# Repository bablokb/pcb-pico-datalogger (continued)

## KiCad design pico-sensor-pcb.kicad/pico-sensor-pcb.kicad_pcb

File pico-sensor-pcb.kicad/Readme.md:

KiCAD-Designfiles for Sensor-PCB
================================

Here are the KiCAD (v6) design-files for the sensor-pcb.

Target components:

  - connectors to pico-datalogger-v2 pcb
  - AHT20
  - BH1750
  - PDM mic
  - connectors for I2C (Adafruit + Pimoroni layout)
  - ON button
  - RUN button
  - 4 buttons or LEDs

Schematic
---------

Layout
------

3D-Views
--------

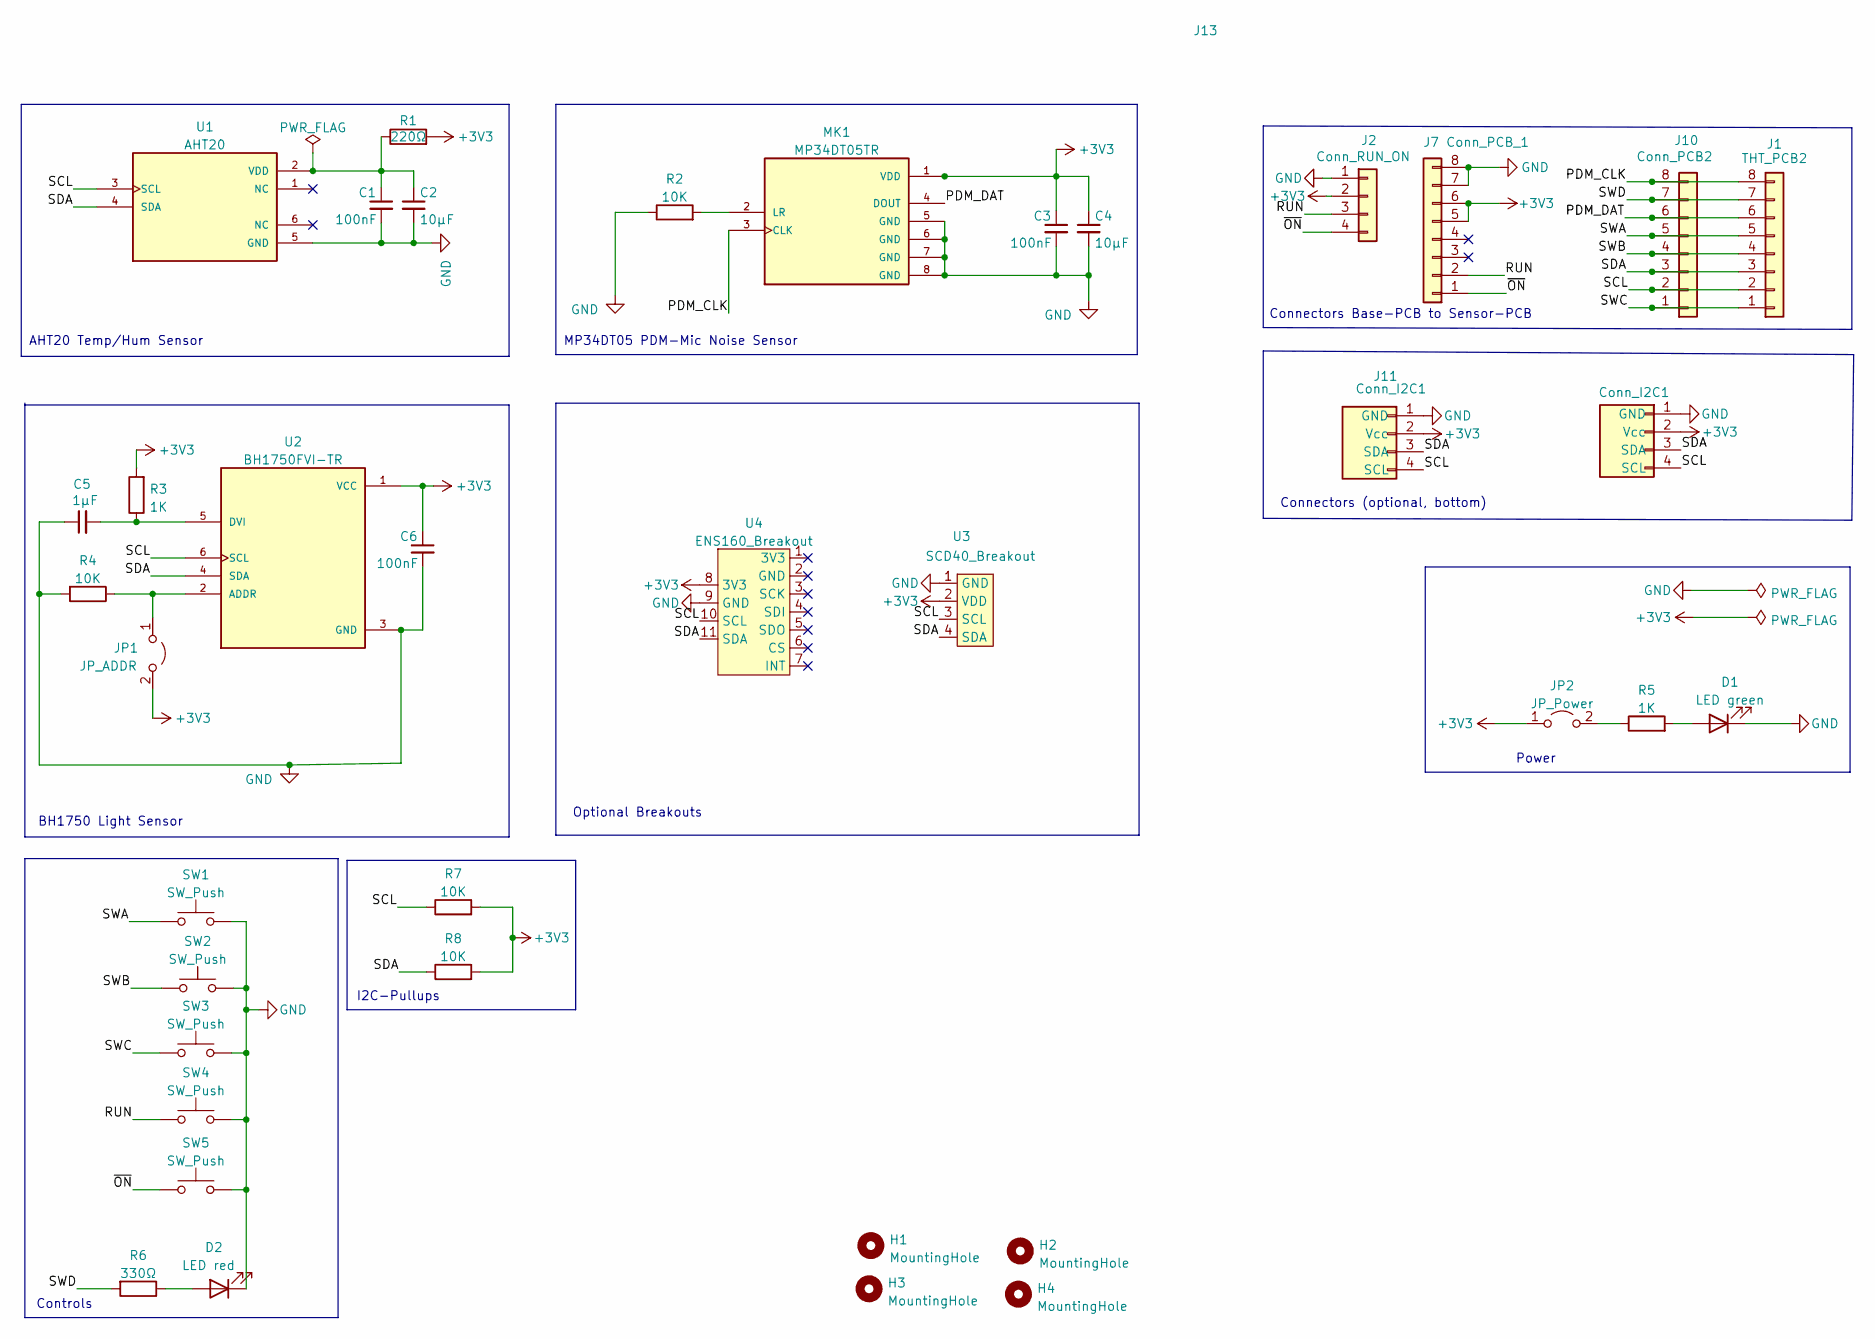
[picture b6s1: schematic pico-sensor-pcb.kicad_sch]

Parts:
C1, C3, C6: 100nF; C_0402_1005Metric; LCSC C1525
C2, C4: 10µF; C_0603_1608Metric; LCSC C19702
C5: 1µF; C_0603_1608Metric; LCSC C15849
D1: LED green; LED_0805_2012Metric; LCSC C2297
D2: LED red; LED_0805_2012Metric; LCSC C84256
H1, H2, H3, H4: MountingHole; MountingHole_2.5mm
J1: THT_PCB2; PinHeader_1x08_P2.54mm_Vertical
J2: Conn_RUN_ON; PinHeader_1x04_P2.54mm_Vertical
J7: Conn_PCB_1; JST_SUR_BM08B-SURS-TF_1x08-1MP_P0.80mm_Vertical; LCSC C5143489
J10: Conn_PCB2; JST_SUR_BM08B-SURS-TF_1x08-1MP_P0.80mm_Vertical; LCSC C5143489
J11: Conn_I2C1; JST_SH_SM04B-SRSS-TB_1x04-1MP_P1.00mm_Horizontal; LCSC C160404
J13: Conn_I2C1; PinHeader_1x04_P2.54mm_Horizontal
JP1: JP_ADDR; SolderJumper-2_P1.3mm_Open_Pad1.0x1.5mm
JP2: JP_Power; SolderJumper-2_P1.3mm_Open_Pad1.0x1.5mm
MK1: MP34DT05TR; LCSC C2688664
R1: 220Ω; R_0402_1005Metric; LCSC C25091
R2, R4, R7, R8: 10K; R_0402_1005Metric; LCSC C25744
R3, R5: 1K; R_0402_1005Metric; LCSC C11702
R6: 330Ω; R_0402_1005Metric; LCSC C25104
SW1, SW2, SW3, SW4, SW5: SW_Push; SW_SPST_B3S-1000; LCSC C221869
U1: AHT20; LCSC C3012622
U2: BH1750FVI-TR; BH1750; LCSC C78960
U3: SCD40_Breakout
U4: ENS160_Breakout

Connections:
+3V3: C3.1, C4.1, C6.1, J2.2, J7.5, J7.6, J11.2 (Vcc), J13.2 (Vcc), JP1.2 (B), JP2.1 (A), MK1.1 (VDD), R1.2, R3.2, R7.2, R8.2, U2.1 (VCC), U3.2 (VDD), U4.8 (3V3)
/PDM_CLK: J1.8, J10.8, MK1.3 (CLK)
/PDM_DAT: J1.6, J10.6, MK1.4 (DOUT)
/RUN: J2.3, J7.2, SW4.1
/SCL: J1.2, J10.2, J11.4 (SCL), J13.4 (SCL), R7.1, U1.3 (SCL), U2.6 (SCL), U3.3 (SCL), U4.10 (SCL)
/SDA: J1.3, J10.3, J11.3 (SDA), J13.3 (SDA), R8.1, U1.4 (SDA), U2.4 (SDA), U3.4 (SDA), U4.11 (SDA)
/SWA: J1.5, J10.5, SW1.1
/SWB: J1.4, J10.4, SW2.1
/SWC: J1.1, J10.1, SW3.1
/SWD: J1.7, J10.7, R6.2
/~ON: J2.4, J7.1, SW5.1
GND: C1.2, C2.2, C3.2, C4.2, C5.1, C6.2, D1.1 (K), D2.1 (K), J2.1, J7.7, J7.8, J11.1 (GND), J13.1 (GND), MK1.5 (GND), MK1.6 (GND), MK1.7 (GND), MK1.8 (GND), R2.1, R4.2, SW1.2, SW2.2, SW3.2, SW4.2, SW5.2, U1.5 (GND), U2.3 (GND), U3.1 (GND), U4.9 (GND)
unnamed: C1.1, C2.1, R1.1, U1.2 (VDD)
unnamed: C5.2, R3.1, U2.5 (DVI)
unnamed: D1.2 (A), R5.2
unnamed: D2.2 (A), R6.1
unnamed: JP1.1 (A), R4.1, U2.2 (ADDR)
unnamed: JP2.2 (B), R5.1
unnamed: MK1.2 (LR), R2.2

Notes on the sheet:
Optional Breakouts
AHT20 Temp/Hum Sensor
BH1750 Light Sensor
MP34DT05 PDM-Mic Noise Sensor
Power
Connectors (optional, bottom)
I2C-Pullups
Controls
Connectors Base-PCB to Sensor-PCB

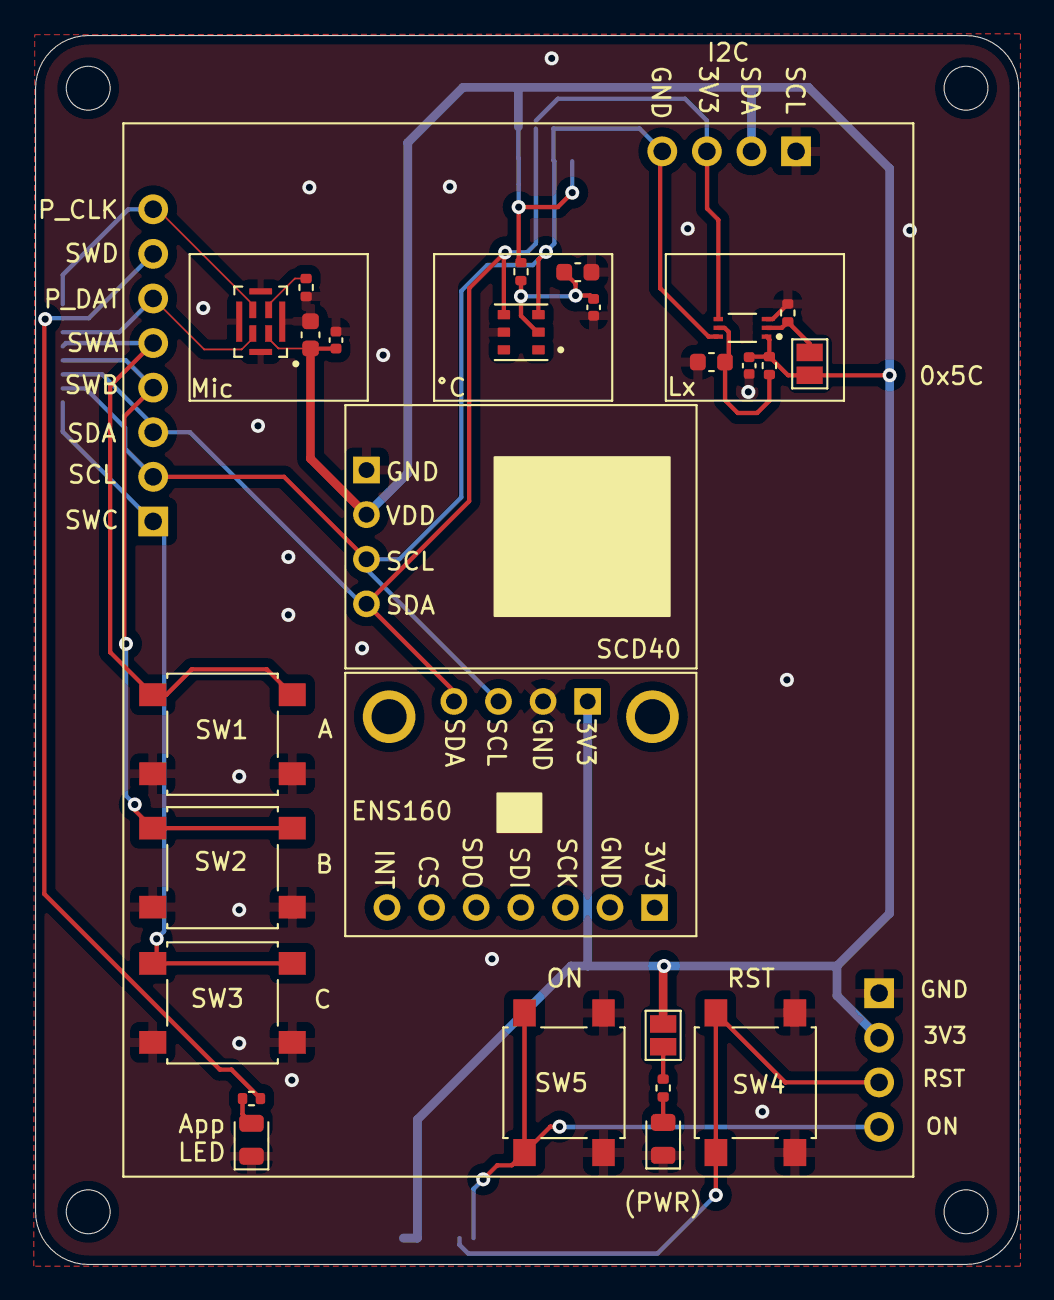
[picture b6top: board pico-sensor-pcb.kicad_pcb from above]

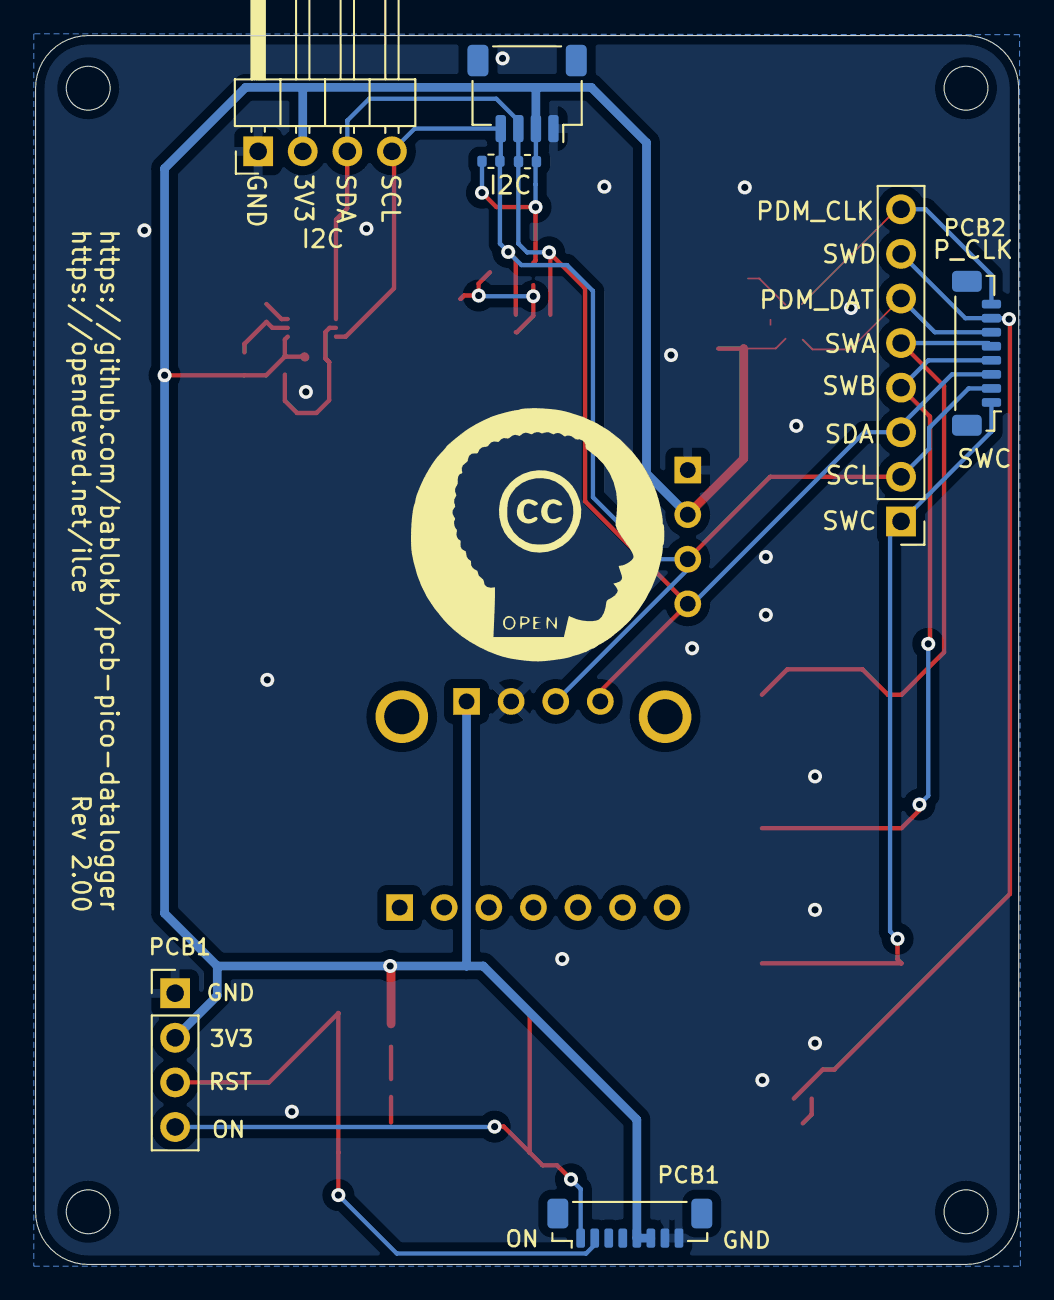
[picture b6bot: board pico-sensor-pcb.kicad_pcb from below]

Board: 2 copper layers, 56.0 x 70.0 mm, 38 parts (8 on the bottom side), 19 nets.

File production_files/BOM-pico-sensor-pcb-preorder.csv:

Comment,Designator,Footprint,LCSC
1K,"R3,R5",R_0402_1005Metric,C11702
100nF,"C1,C3,C6",C_0402_1005Metric,C1525
1µF,C5,C_0603_1608Metric,C15849
Conn_I2C1,J11,JST_SH_SM04B-SRSS-TB_1x04-1MP_P1.00mm_Horizontal,C160404
10µF,"C2,C4",C_0603_1608Metric,C19702
SW_Push,"SW1,SW2,SW3,SW4,SW5",SW_SPST_B3S-1000,C221869
LED green,D1,LED_0805_2012Metric,C2297
220Ω,R1,R_0402_1005Metric,C25091
330Ω,R6,R_0402_1005Metric,C25104
10K,"R2,R4,R7,R8",R_0402_1005Metric,C25744
MP34DT05TR,MK1,MP34DT05TR,C2688664
AHT20,U1,AHT20,C2757850
Conn_PCB2,"J10,J7",JST_SUR_BM08B-SURS-TF_1x08-1MP_P0.80mm_Vertical,C5143489
BH1750FVI-TR,U2,BH1750,C78960
LED red,D2,LED_0805_2012Metric,C84256

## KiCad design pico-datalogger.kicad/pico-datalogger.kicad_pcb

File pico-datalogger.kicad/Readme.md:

KiCAD-Designfiles
=================

This branch contains KiCAD v7 files. The PCB layout has been adjusted to fit a 10th inch grid. The only significant adjustment was to move SWA, SWB, SWC to a new location.

The diagrams below are for the older version KiCAD (v6). 

Schematic
---------

Layout
------

3D-Views
--------

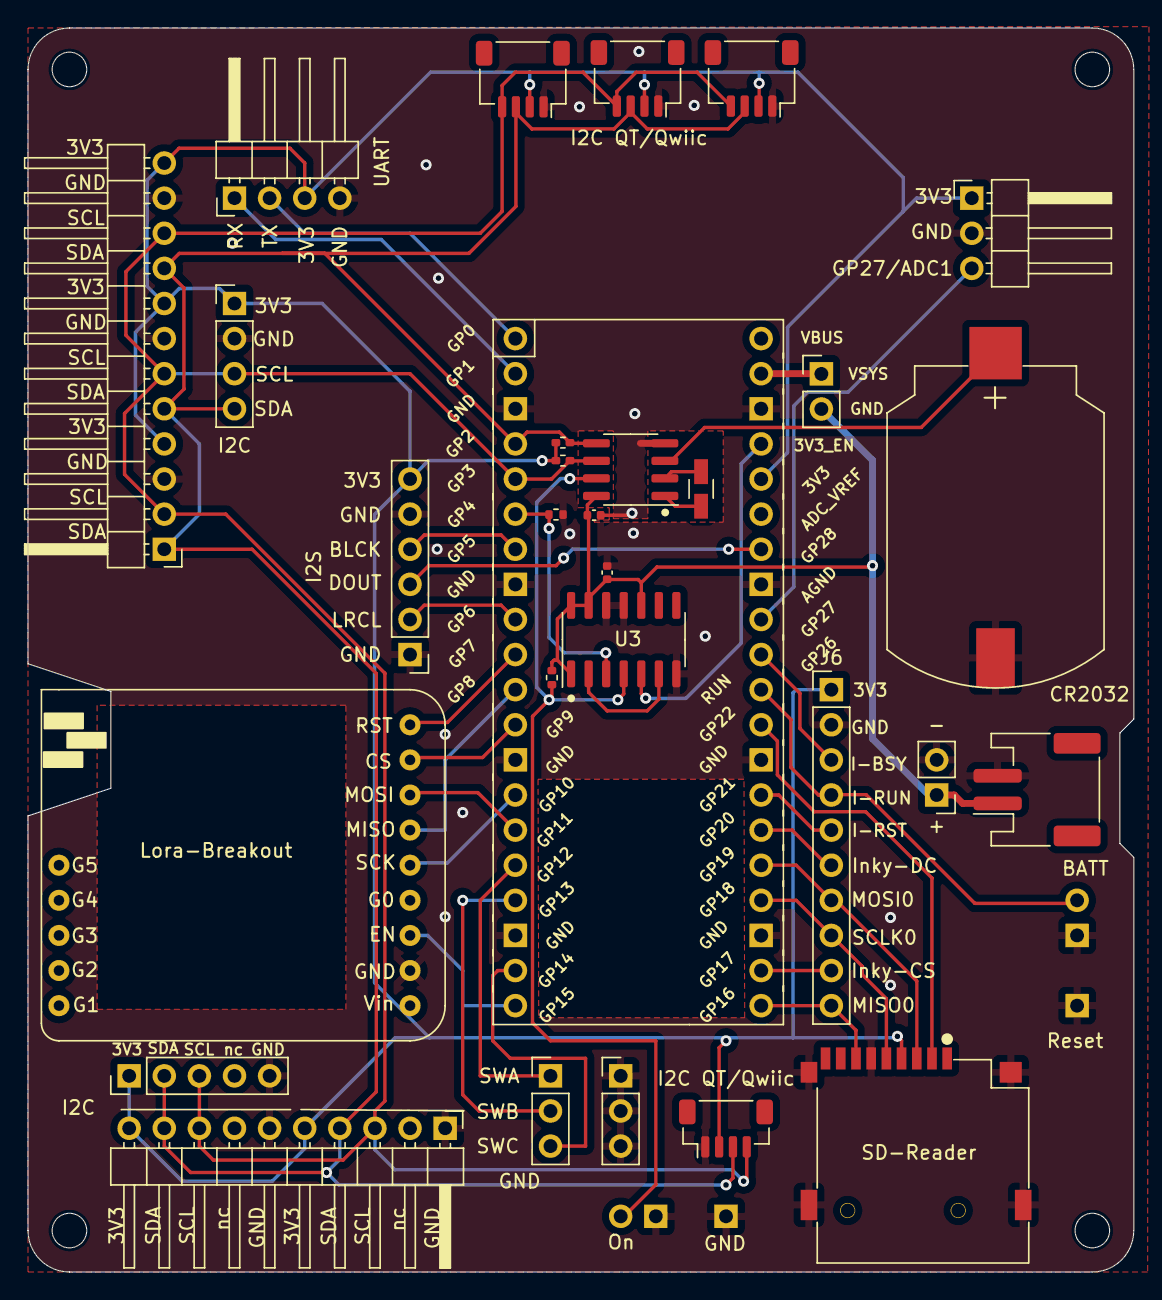
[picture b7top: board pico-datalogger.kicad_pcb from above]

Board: 2 copper layers, 80.0 x 90.0 mm, 36 parts (0 on the bottom side), 37 nets.

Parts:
BT1: Coin_Cell; CR2032_Holder
C1, C2: 100nF; C_0402_1005Metric
H1, H2, H3, H4: MountingHole; MountingHole_2.5mm
J1: JST-PH2 VCC; JST_PH_S2B-PH-SM4-TB_1x02-1MP_P2.00mm_Horizontal
J2: I2C_8; JST_SH_SM04B-SRSS-TB_1x04-1MP_P1.00mm_Horizontal
J3: RFM9x_Lora_Breakout
J4: Alt-VCC; PinHeader_1x02_P2.54mm_Vertical
J5: Conn_I2S; PinHeader_1x06_P2.54mm_Vertical
J6: Conn_Inky_SPI; PinHeader_1x10_P2.54mm_Vertical
J7: Micro_SD_TF_PUSH; TF-Push
J8: Conn_ADC; PinHeader_1x03_P2.54mm_Horizontal
J9: Conn_UART; PinHeader_1x04_P2.54mm_Horizontal
J10: Conn_Inky_SW; PinHeader_1x03_P2.54mm_Vertical
J11: I2C_1; PinHeader_1x12_P2.54mm_Horizontal
J12: I2C_7; JST_SH_SM04B-SRSS-TB_1x04-1MP_P1.00mm_Horizontal
J14: I2C_6; JST_SH_SM04B-SRSS-TB_1x04-1MP_P1.00mm_Horizontal
J16: BG_2; PinHeader_1x05_P2.54mm_Vertical
J18: I2C_5; JST_SH_BM04B-SRSS-TB_1x04-1MP_P1.00mm_Vertical
J19: I2C_4; PinHeader_1x04_P2.54mm_Vertical
J20: BG_3; PinHeader_1x10_P2.54mm_Horizontal
J21: Conn_GND; PinHeader_1x03_P2.54mm_Vertical
JP1: Jumper_VSYS; PinHeader_1x02_P2.54mm_Vertical
R1: 100K; R_0402_1005Metric
R2, R3, R4: 10K; R_0402_1005Metric
SW1: SW_Push_SLIM; SW_PUSH_SLIM_1x4
SW2: SW_Reset; SW_PUSH_SLIM_1x4
U1: SN74HC74N; SOIC-14_3.9x8.7mm_P1.27mm
U2: PCF8523T; SOIC-8_3.9x4.9mm_P1.27mm
U3: Pico; RPi_Pico_TH_nodbg
Y1: Crystal; Crystal_SMD_3215-2Pin_3.2x1.5mm

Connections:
+3V3: J2.2 (Vcc), J3.1 (VIN), J5.6, J6.1, J7.4 (VDD), J8.1, J9.3, J11.4, J11.8, J11.12, J12.2 (Vcc), J14.2 (Vcc), J16.1, J18.2 (Vcc), J19.1, J20.5, J20.10, R3.1, R4.1, U3.36 (3V3)
+BATT: C1.1, C2.1, J1.1, J4.1, JP1.2 (B), R2.1, U1.1 (1~CLR), U1.10 (2~PRE), U1.13 (2~CLR), U1.14 (VCC), U2.8 (VDD)
/1~PRE: R2.2, SW1.2, U1.4 (1~PRE), U2.7 (~INT1/CLKOUT)
/3V3_EN: U1.5 (1Q), U3.37 (3V3_EN)
/BLCK: J5.4, U3.7 (GPIO5)
/DOUT: J5.3, U3.34 (GPIO28_ADC2)
/GP4_DONE: R1.2, U1.3 (1CLK), U3.6 (GPIO4)
/GP27_ADC1: J8.3, U3.32 (GPIO27_ADC1)
/Inky_BUSY: J6.3, U3.31 (GPIO26_ADC0)
/Inky_CS: J6.9, U3.22 (GPIO17)
/Inky_DC: J6.6, U3.26 (GPIO20)
/Inky_RST: J6.5, U3.27 (GPIO21)
/Inky_RUN: J6.4, SW2.2, U3.30 (RUN)
/Inky_SWA: J10.1, U3.16 (GPIO12)
/Inky_SWB: J10.2, U3.17 (GPIO13)
/Inky_SWC: J10.3, U3.19 (GPIO14)
/LRCL: J5.2, U3.9 (GPIO6)
/Lora_CS: J3.8 (CS), U3.12 (GPIO9)
/Lora_EN: J3.3 (EN), U3.20 (GPIO15)
/Lora_RST: J3.9 (RST), U3.10 (GPIO7)
/MISO0: J6.10, J7.7 (DAT0), U3.21 (GPIO16)
/MISO1: J3.6 (MISO), U3.11 (GPIO8)
/MOSI0: J6.7, J7.3 (CMD), U3.25 (GPIO19)
/MOSI1: J3.7 (MOSI), U3.15 (GPIO11)
/RX: J9.1, U3.2 (GPIO1/RX)
/SCL: J2.4 (SCL), J11.2, J11.6, J11.10, J12.4 (SCL), J14.4 (SCL), J16.3, J18.4 (SCL), J19.3, J20.3, J20.8, R4.2, U2.6 (SCL), U3.5 (GPIO3)
/SCLK0: J6.8, J7.5 (CLK), U3.24 (GPIO18)
/SCLK1: J3.5 (SCK), U3.14 (GPIO10)
/SDA: J2.3 (SDA), J11.1, J11.5, J11.9, J12.3 (SDA), J14.3 (SDA), J16.2, J18.3 (SDA), J19.4, J20.4, J20.9, R3.2, U2.5 (SDA), U3.4 (GPIO2)
/SD_CS: J7.2 (DAT3/CD), U3.29 (GPIO22)
/TX: J9.2, U3.1 (GPIO0/TX)
/VSYS: JP1.1 (A), U3.39 (VSYS)
GND: BT1.2 (-), C1.2, C2.2, J1.2, J2.1 (GND), J3.2 (GND), J4.2, J5.1, J5.5, J6.2, J7.6 (VSS), J7.10 (SHIELD), J7.11 (SHIELD), J7.12 (SHIELD), J7.13 (SHIELD), J8.2, J9.4, J11.3, J11.7, J11.11, J12.1 (GND), J14.1 (GND), J16.5, J18.1 (GND), J19.2, J20.1, J20.6, J21.1, J21.2, J21.3, R1.1, SW1.1, SW2.1, U1.7 (GND), U1.11 (2CLK), U1.12 (2D), U2.4 (VSS), U3.3 (GND), U3.8 (GND), U3.13 (GND), U3.18 (GND), U3.23 (GND), U3.28 (GND), U3.33 (AGND), U3.38 (GND)
unnamed: BT1.1 (+), U2.3 (VBAT)
unnamed: U1.2 (1D), U1.6 (1~Q)
unnamed: U2.1 (OSCI), Y1.2
unnamed: U2.2 (OSCO), Y1.1

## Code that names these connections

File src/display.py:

#-----------------------------------------------------------------------------
# Manage update of display.
#
# Author: Bernhard Bablok
#
# Website: https://github.com/pcb-pico-datalogger
#-----------------------------------------------------------------------------

import pins
from log_writer import Logger

import displayio
from dataviews.DisplayFactory import DisplayFactory

g_logger = Logger()

class Display:
  """ prepare and update display for the datalogger """

  # --- constructor   --------------------------------------------------------

  def __init__(self,config,spi):
    """ constructor """

    self._config = config
    self._spi    = spi
    self._view   = None

    # spi - if not already created
    if not self._spi:
      self._spi = busio.SPI(pins.PIN_SD_SCK,pins.PIN_SD_MOSI)

    displayio.release_displays()
    if config.HAVE_DISPLAY == "Inky-Pack":
      self._display = DisplayFactory.inky_pack(self._spi)
    elif config.HAVE_DISPLAY == "Ada-2.13-Mono":
      self._display = DisplayFactory.ada_2_13_mono(
        pin_dc=pins.PIN_INKY_DC,pin_cs=pins.PIN_INKY_CS,
        pin_rst=pins.PIN_INKY_RST,pin_busy=pins.PIN_INKY_BUSY,spi=self._spi)
    elif config.HAVE_DISPLAY == "Ada-1.54-Mono":
      self._display = DisplayFactory.ada_1_54_mono(
        pin_dc=pins.PIN_INKY_DC,pin_cs=pins.PIN_INKY_CS,
        pin_rst=pins.PIN_INKY_RST,pin_busy=pins.PIN_INKY_BUSY,spi=self._spi)
    elif config.HAVE_DISPLAY == "Display-Pack":
      self._display = DisplayFactory.display_pack(self._spi)
      self._display.auto_refresh = False
    else:
      g_logger.print(f"unsupported display: {config.HAVE_DISPLAY}")
      config.HAVE_DISPLAY = None
    self._view = None

  # --- create view   ---------------------------------------------------------

  def create_view(self,formats):
    """ create data-view """

    if self._view:
      return

    g_logger.print("start: _create_view")

    from dataviews.Base import Color, Justify
    from dataviews.DataView  import DataView
    from dataviews.DataPanel import DataPanel, PanelText

    # guess best dimension
    n_formats = len(formats)
    if n_formats < 5:
      dim = (2,2)
    elif n_formats < 7:
      dim = (3,2)
    else:
      dim = (3,4)

    if n_formats < dim[0]*dim[1]:
      formats.extend(
        ["" for _ in range(dim[0]*dim[1] - n_formats)])
    elif n_formats > dim[0]*dim[1]:
      g_logger.print(f"only displaying first {dim[0]*dim[1]/2:.0f} sensor-values")
      del formats[dim[0]*dim[1]:]

    border  = 1
    divider = 1
    padding = 5
    self._view = DataView(
      dim=dim,
      width=self._display.width-2*border-(dim[1]-1)*divider,
      height=int(0.6*self._display.height),
      justify=Justify.LEFT,
      fontname=f"fonts/{self._config.FONT_DISPLAY}.bdf",
      formats=formats,
      border=border,
      divider=divider,
      color=Color.BLACK,
      bg_color=Color.WHITE
    )

    for i in range(0,dim[0]*dim[1],2):
      self._view.justify(Justify.LEFT,index=i)
      self._view.justify(Justify.RIGHT,index=i+1)

    # create DataPanel
    title = PanelText(text=f"{self._config.LOGGER_TITLE}",
                      fontname=f"fonts/{self._config.FONT_DISPLAY}.bdf",
                      justify=Justify.CENTER)

    self._footer = PanelText(text=f"Updated: ",
                             fontname=f"fonts/{self._config.FONT_DISPLAY}.bdf",
                             justify=Justify.RIGHT)
    self._panel = DataPanel(
      width=self._display.width,
      height=self._display.height,
      view=self._view,
      title=title,
      footer=self._footer,
      border=border,
      padding=5,
      justify=Justify.CENTER,
      color=Color.BLACK,
      bg_color=Color.WHITE
    )
    self._display.root_group = self._panel

    g_logger.print("end:  _create_view")

  # --- set values for ui   --------------------------------------------------

  def set_values(self,values,footer):
    """ set values """

    self._view.set_values(values)
    self._footer.text = footer

  # --- refresh the display   ------------------------------------------------

  def refresh(self):
    """ refresh display """
    self._display.refresh()

  # --- create simple ui   ---------------------------------------------------

  def create_simple_view(self):
    """ create simple view of a single DisplayText """

    if self._view:
      return

    g_logger.print("start: _create_simple_view")

    from adafruit_bitmap_font import bitmap_font
    from adafruit_display_text import label as label
    from vectorio import Rectangle

    font = bitmap_font.load_font(f"fonts/{self._config.FONT_DISPLAY}.bdf")
    self._view = displayio.Group()
    shader = displayio.Palette(2)
    shader[0] = 0xFFFFFF
    shader[1] = 0x000000
    self._view.append(Rectangle(pixel_shader=shader,x=0,y=0,
                   width=self._display.width,
                   height=self._display.height,
                   color_index=0))
    m = label.Label(text="ABCD: 23.5",font=font)         # 10 chars
    self._max_chars = 10*self._display.width/m.width      # round later
    self._panel = label.Label(font=font,color=shader[1],
                              tab_replacement=(2," "),
                              line_spacing=0.8,
                              text=60*'M',anchor_point=(0.5,0.5))
    self._panel.anchored_position = (self._display.width/2,
                                     self._display.height/2)
    self._view.append(self._panel)
    g_logger.print("end:   _create_simple_view")

  # --- set ui-text for simple-ui   ------------------------------------------

  def set_ui_text(self,csv_header,record):
    """ set text of simple UI """

    # create dynamic format: width of label is widh - 4 - 1 (4:value, 1:colon)
    # layout is four columns: label:value label:value
    w = int((self._max_chars-1)/2)
    template1 = "{label:<"+f"{w-5}.{w-5}"+"}:{value:>4.4}"
    template2 = "{label:<"+f"{w-4}.{w-4}"+"}:{value:>4.4}"
    columns = csv_header.split('#')[-1].split(',')
    merged = zip(columns,record.split(','))

    # collect output into string
    ui_string = f"{self._config.LOGGER_TITLE}"
    ui_line = ""

    for label,value in merged:
      if "°" in label:
        # workaround for CP bug (issue #8171)
        template = template2
      else:
        template = template1
      if label == "ts":
        ts_line = f"\nat {value}"
      elif label == "ID":
        pass                 # skip ID (should be part of title)
      elif ui_line:          # second column
        ui_string += f"\n{ui_line} "+template.format(label=label,value=value)
        ui_line = ""
      else:
        ui_line = template.format(label=label,value=value)

    if ui_line:
      ui_string += f"\n{ui_line}"
    ui_string += ts_line
    g_logger.print(ui_string)
    self._panel.text = ui_string
    self._display.root_group = self._view

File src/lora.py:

# -----------------------------------------------------------------------------
# LoRa TX and RX using adafruit_rfm9x.py in /lib folder.
#
# Authors: Syed Omer Ali, Björn Haßler
#
# Website: https://github.com/pcb-pico-datalogger
# -----------------------------------------------------------------------------

import digitalio
import busio
import time
import adafruit_rfm9x
import config
from log_writer import Logger
g_logger = Logger()
import board
from digitalio import DigitalInOut, Direction, Pull

class LORA:

    def __init__(self, freq=433.0):
        """ constructor """

        try:
            from log_config import g_logger
        except:
            from log_writer import Logger
            g_logger = Logger('console')


        # Lora interface (SPI, separate)
        PIN_LORA_CS = board.GP9
        PIN_LORA_RST = board.GP7
        PIN_LORA_EN = board.GP15
        PIN_LORA_SCK = board.GP10
        PIN_LORA_MOSI = board.GP11
        PIN_LORA_MISO = board.GP8

        NODE_ADDRESS = config.NODE_ADDRESS                      # Node address                                                                                                                                             
        BASE_STATION_ADDRESS = config.BASE_STATION_ADDRESS      # Base statio=n address                                                                                                                                    
        #LORA_RANGE_TEST = False             # If this is true, the logger does not undertake the usual functions, but just runs the range test.                                                        
        LORA_ENABLE_TIME = 0                 # wait time between switching on module and lora device registration                                                                                       
        LORA_WAIT_AFTER_SEND = 0             # wait time after sending     

        try:
            g_logger.print("Setting up SPI1")
            spi1 = busio.SPI(PIN_LORA_SCK, PIN_LORA_MOSI, PIN_LORA_MISO)
            CS = DigitalInOut(PIN_LORA_CS)
            RESET = DigitalInOut(PIN_LORA_RST)
            ENABLE = DigitalInOut(PIN_LORA_EN)
            ENABLE.direction  = Direction.OUTPUT
            #self.lora = lora.LORA(433.0, self._spi1, CS, RESET, ENABLE)
            # payload = self.csv_header + "\n" + self.record

            # Define pins connected to the chip, use these if wiring up the breakout according to the guide:
            g_logger.print("Enabling rfm9x on SPI1")
            ENABLE.value = 1
            time.sleep(LORA_ENABLE_TIME)
            g_logger.print("Initializing rfm9x on SPI1")
            self.rfm9x = adafruit_rfm9x.RFM9x(
                spi1, CS, RESET, freq, baudrate=100000)
            g_logger.print("Detected rfm9x on spi")
            # enable CRC checking
            self.rfm9x.enable_crc = True
            # You can however adjust the transmit power (in dB).  The default is 13 dB but
            # high power radios like the RFM95 can go up to 23 dB:
            #self.rfm9x.tx_power = 23
            # set delay before transmitting ACK (seconds)
            self.rfm9x.ack_delay = 0.1
            self.rfm9x.node = NODE_ADDRESS                 # node or this device
            self.rfm9x.destination = BASE_STATION_ADDRESS  # base station or destination
            self.rfm9x.ack_wait = 0.5 # (defaults to 0.5ms)
            #This sets the delay before retrying transmission of a packet after no ACK has been received.
            self.rfm9x.ack_retries = 3 # (defaults to 5 retries)
            #Set the number or retries to attempt if no ACK message is received.
        except Exception as ex:
            g_logger.print(f"exception: {ex}")

    def transmit(self, header, string):
        g_logger.print("LoRa transmit")
        message = self.rfm9x.send_with_ack(bytes(string, "UTF-8"))
        g_logger.print("Success? "+str(message))

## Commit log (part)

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2024-07-26 port RTC-configuration from datacollector
2024-07-26 move definition of self.done to shutdown()
2024-07-26 added task documentation
2024-07-26 sensor-specs must have 'x' or 'X' in address
2024-07-27 documented RTC setup
2024-07-27 minor changes and additions
2024-07-29 added pins for SW_A and SW_D (LED)
2024-07-29 fix phat method
2024-07-30 fix examples
2024-07-30 fix logger import
2024-07-30 document configuration for buttons
2024-07-30 make OLED a singleton class
2024-07-30 fix property names
2024-07-30 add wrapper ('main program') for tools/scd4x_config.py
2024-07-30 added scripts in tools/
2024-07-30 replace board.xxx with pins.xxx
2024-07-31 use lowercase-keys for properties and keys in data-dict
2024-08-01 add set_target(): make logging-target configurable at runtime
2024-08-01 turn of logging during data-collection
2024-08-01 provide (and use) pre-formatted sensor-output in data-dict
2024-08-02 support SENSORS_CSV_ONLY
2024-08-02 reset init_time after first cycle
2024-08-02 added default for HAVE_I2C_MP
2024-08-02 added documentation for HAVE_I2C_MP
2024-08-02 added support for I2C-multiplexers
2024-08-02 add I2C-multiplexer support to core software functions
2024-08-03 added None as valid value for HAVE_RTC
2024-08-03 first objects for Stevenson-Screen adapter
2024-08-04 code cleanup: self.ignore is not relevant in constructor
2024-08-05 add links to examples
2024-08-05 fix syntax error
2024-08-05 cleanup example
2024-08-05 fixed link to open-meteo
2024-08-05 first iteration of datalogger-holder
2024-08-05 renamed shared_modules.scad -> stevenson_holder.scad
2024-08-06 change default altitude
2024-08-06 switch sensor off in strobe mode or cont. mode with deep-sleep
2024-08-06 new iteration
2024-08-06 rework multi-sample code
2024-08-07 support USER_LIBS variable
2024-08-07 document SCD4X_INTERVAL
2024-08-08 show create command of commit.py
2024-08-08 updated to support CP 8.x and 9.x
2024-08-08 implement SCD4X_INTERVAL
2024-08-09 set DISCARD=1 for SAMPLES==1
2024-08-09 add missing 'ts,' to CSV-header
2024-08-10 reduce cutouts for lora-pcb-holder
2024-08-10 fine-tune cutouts for stevenson-holder and battery-cage
2024-08-10 added src/lib
2024-08-12 support both CP8 and CP9
2024-08-12 document usage of non-distributed versions of mpy-cross
2024-08-15 change comment: clarify use of PCB_VERSION
2024-08-16 support column-row layout
2024-08-16 compensate for pressure (needs BMx280)
2024-08-16 document new sensor configuration features
2024-08-17 don't create top-level object to allow use/include
2024-08-17 support CP-versions without alarm-module
2024-08-19 documented MHZ19
2024-08-20 first iteration of battery-cage
2024-08-21 support additional kwargs in factory-methods
2024-08-21 fix wifi reuse
2024-08-22 added holder-module for M5-Stack CO2-sensor
2024-08-22 next iteration / refactoring of dimensions to separate files
2024-09-05 don't create top-level object
2024-09-05 copied design from other project to integrate into sensor-holder
2024-09-17 add cutout for buttons
2024-11-09 add wrapper and libs for new sensor MHZ-19x
2024-11-09 also display OLED for given time when INTERVAL > 60, i.e. with deep-sleep
2024-11-19 renamed src.blues_gateway/lib to src.blues_gateway/lib8
2024-11-19 use existing LoRa-singleton without configuration
2024-11-19 document GW_?X_TYPE variables
2024-11-19 renamed src.blues_gateway to src.gateway
2024-11-22 removed executable flag
2024-11-22 added additional libraries needed for new implementation
2024-11-22 setup() only create spi if not already created
2024-11-22 create noop gateway sender
2024-11-22 added basic tasks (time-update, sd-write, oled-update)
2024-11-22 code refactoring: move HW-init to src/hw_helper.py
2024-11-25 added settings.py to SOURCES2
2024-11-25 add logger to constructor, fix some defaults
2024-11-25 pass logger to Settings()
2024-11-25 add log-messages, rethrow exceptions
2024-11-25 use hw_helper
2024-11-25 bugfix: wrong raise syntax
2024-11-26 print initial 'waiting...' message to OLED
2024-11-26 _update_oled(): print multiple fields on last line
2024-11-26 remove initial sleep (now within log_writer)
2024-12-02 bugfix: add pins to hw_helper.init_rtc()
2024-12-02 renamed docs/software.md to docs/software_datalogger.md
2024-12-02 link to standard HW-configuration
2024-12-02 bugfix: remove unused import for alarm
2024-12-02 create sd-directory
2024-12-03 fixed spelling: package->packet
2024-12-03 implement _set_wakeup()
2024-12-03 create or remove /sd depending on CP version
2024-12-04 updated to new standard
2024-12-04 assume all config-attributes exist
2024-12-04 add section about building the gateway firmware
2024-12-05 sleep before instead of after sending packet (promptly display updates)
2024-12-05 don't trace exception if netupdate fails
2024-12-05 defince SDA/SCL as SDA1/SCL1
2024-12-06 define PIN_RX, PIN_TX
2024-12-09 shutdown(): catch possible exceptions
2024-12-10 migrated from ACTIVE_WINDOW_START/...END to time-table based operation
2024-12-10 calculate sleep-duration from wakeup time
2024-12-10 prefix log-messages with 'rtc:'
2024-12-10 removed src/lib9/rtc_ext
2024-12-10 link src/lib9/rtc_text to ../lib8/rtc_ext
2024-12-10 create shared libraries as links
2024-12-10 copy files/dirs to DEPLOY_TO instead of symlinks
2024-12-10 add notecard-library to lib9
2024-12-12 nonfunctional: fix name within comment
2024-12-14 removed unused variables
2024-12-14 add support for NoopReceiver
2024-12-16 fixed markup
2024-12-17 initial version of datalogger-receiver service
2024-12-17 support short options, add -d/--debug for print_err()
2025-01-16 document receiver-service and add links to it
2025-01-18 bugfix _sleep_impl(): use 'until' instead of 'ep_alarm'
2025-02-11 make normal-sleep limit a constant
2025-03-21 enter bootloader-mode with button C
2025-03-21 updated and sorted
2025-03-21 new default version: CP_VERSION=9
2025-03-24 import v9 display classes/modules
2025-03-24 use newest version of dataviews-library
2025-04-13 added SURS-cable-tester PCB
2025-04-23 add support for WeAct-2.9in display
2025-05-28 adafruit_display_shapes: removed unused modules to save flash-space
2025-06-05 minor correction regarding INTERVAL
2025-06-05 preliminary support for SEN66
2025-06-05 always use mpy-cross from bin/
2025-06-05 move rtc_ext/ from lib8/ to src/
2025-06-05 added pre-compiled version of the rtc_ext-module
2025-06-05 add Readme to the source-directory for rtc_ext
2025-06-06 refactor most of the code to broadcast_impl.py (allows pre-compilation)
2025-06-10 add pm number concentration
2025-06-16 remove unneeded wait for first measurement (alreay have init_time)
2025-06-23 document SEN66; update PMS5003
2025-06-23 support sensor-configuration
2025-06-24 simple 'case' for Adalogger perfboard pcb
2025-06-24 add SEN6x configuration tool
2025-07-22 added images for SURS-cable-tester
2025-09-01 implement FORCE_RESET
2025-10-24 remove udp_gateway.py from tools/ (use src.receiver_service instead)
2025-10-24 document sen6x_config
2025-10-31 add support for CircuitPython 10.x.x
2025-10-31 removed last CP8 leftovers
2025-11-12 fix pin-order for SEN66-connector
2025-11-12 switch to user:JST-PH2
2025-11-12 switch to user:JST-SH4
2025-11-12 switch to user:SW_PUSH
2025-11-12 switch to user:JST_SUR_BM08B-SURS-TF_1x08-1MP_P0.80mm_Vertical
2025-11-12 improved silkscreen
2025-11-13 move AA-holder away from mounting-hole
2025-11-18 initial routing of power and I2C-devices
2025-11-18 initial routing display-connector, on/rst buttons
2025-11-20 swapped additional pins to simplify routing
2025-11-21 fine tune AHT20 layout and add cutout
2025-11-21 fixes for production files
2025-11-21 changes due to production-file generation
2025-11-30 use 868-version of LoRa-chip (for iteration-1)
2025-12-02 always copy log_config.py and config.py
2025-12-02 add atexit-processing to free SPI-pins
2025-12-05 added not about recommended CircuitPython version
2025-12-08 cleanup of lib-directories
2025-12-08 refactoring: make object public
2025-12-09 gateway: deploy tasks
2025-12-09 updated configuration template
2025-12-09 add atexit-processing to free spi
2025-12-09 refactored data-processing to tasks/
2025-12-09 unify naming conventions for config-variables
2025-12-09 _process_data(): support alternative task-lists
2025-12-10 clean: ignore errors
2025-12-10 fix: check if values exist and their type
2025-12-10 add atexit-processing for oled
2025-12-10 transmit(): trace elapsed time
2025-12-10 implement basic broadcast-tasks
2025-12-11 collect, save and show technical infos during broadcast
2025-12-12 automatic calcuation of receive-timeout (tentative)
2025-12-12 transmit(): never send with ack, prepend msg_type to payload
2025-12-12 update all lora.transmit() method calls
2025-12-12 fixed 3D model for battery-holder
2025-12-12 added images
2025-12-12 minor wording change in log-message
2025-12-12 implement handle_data() with processing of S-messages
2025-12-12 enhance receive()/transmit(): extract sender, support keep_listening
2025-12-12 new logic: use S-messages
2025-12-13 changed QOS parameter
2025-12-15 fixed calculation of time-factor
2025-12-15 receive(): don't clear FIFO/interrupt with timeout
2025-12-15 replace LORA_RECEIVE_TIMEOUT with LORA_GW_RECEIVE_TIMEOUT
2025-12-15 use LORA_GW_RECEIVE_TIMEOUT
2025-12-15 fix: receive() needs timeout with keyword
2025-12-15 set xmit_timeout based on expected transmission time
2025-12-15 remove LORA_ACK*, add LORA_QOS
2025-12-15 updated docs and templates for LoRa
2025-12-16 removed (incomplete) task 'send_lora_18.py'
2025-12-16 removed LORA_ENABLE_TIME
2025-12-16 save failed records and resend later
2025-12-16 optimized T/B messages
2025-12-16 added/updated documents
2025-12-18 add pin-mapping for PCB-v3
2025-12-20 add support for 'LM66200'-sensor
2025-12-22 add send(): send data using TCP
2025-12-22 added tasks 'buffer_data' and 'send_tcp'
2025-12-25 moved shared code to src.shared/
2025-12-26 document gateway-tasks
2025-12-27 fall back to deep-sleep without PM
2025-12-28 support code in src.shared/
2025-12-28 respect ON_DURATION=0; support GW_TX_TYPE=TCP
2025-12-28 refactored to gw_tx_tcp.py
2025-12-28 add dedicated document about the gateway
2025-12-30 add boot.py for gateway operation
2025-12-30 moved (most of) src/www to src.shared/www
2025-12-30 add web-support for the gateway
2025-12-30 add artifacts needed for web-admin interface
2025-12-30 added files needed for web-admin interface
2026-01-02 add pins for (optional) SD-breakout
2026-01-02 document v3-hardware
2026-01-02 renamed v3-images
2026-01-07 move pins?.py to src.shared
2026-01-09 add link to LoRaWAN regional parameters document
2026-01-10 moved notecard-libs to src.misc
2026-01-10 only compile a single pins-file
2026-01-11 moved src/rtc_ext to src.misc
2026-01-11 moved src/lib9 to src.shared/lib9
2026-01-11 removed (link) src/lib10
2026-01-11 recreated (symlinks) in src/ and src.gateway/ to lib-directories from src.shared/
2026-01-11 added symlink from src.shared/lib10 to lib9
2026-01-12 add support for Tasmota power monitoring
2026-01-12 support INTERVAL=0 for no-delay continuous mode
2026-01-12 refactored release of OLED to OLED-constructor
2026-01-12 add timeout, fix csv
2026-01-12 tm_power: link to core_config_sensors.md for configuration
2026-01-14 take elapsed time into account for interval-based sampling
2026-01-14 updated information for INTERVAL=0
2026-01-15 updated production-files for datalogger-v3 (with rfm95-868)
2026-01-21 return missing values instead of 'None'
2026-01-23 _fetch_time(): check if time_url is configured
2026-01-23 updated compiled version of ext_base.py
2026-01-24 allow primary display and OLED in strobe-mode
2026-01-25 added folder build-template with template-files
2026-01-25 add rotation support for OLED
2026-01-26 copy sensor_meta.py from src.shared
2026-01-26 fix: extract id as contents of item (which is a single value list)
2026-01-26 convert string data to float/int if possible
2026-01-26 implement simple csv to json converter
2026-01-27 add top-level scad-program with all components
2026-01-27 close response/socket in case of problems
2026-01-27 fix tm_power.py (editor wasn't saved)
2026-01-29 removed now unused program-option '--outfile'
